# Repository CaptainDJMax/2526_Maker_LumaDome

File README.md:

# 2526_Maker_LumaDome

##  Présentation du projet
**LumaDome** est une lampe d'ambiance connectée et intelligente. L'objectif est d'allier esthétique et technique pour afficher des messages dynamiques. Conçue comme un objet design hybride, elle associe une base imprimée en 3D, un abat-jour textile structuré par découpe laser et l'électronique sur mesure et la gestion d'énergie.

Au-delà de l'esthétique, l'objectif est de créer une interface lumineuse capable de :
* Afficher des **notifications visuelles** (ex: simulateur d'aube au réveil).
* Diffuser des **messages personnalisés** envoyés en Bluetooth depuis un smartphone.
* Être totalement **nomade** grâce à une batterie intégrée.

## 🛠 Architecture Technique
Ce projet mobilise 4 axes principaux :
1.  **Mécanique :** Base cylindrique (Impression 3D) contenant l'électronique + Structure haute (Découpe Laser) supportant le textile.
2.  **Électronique :** PCB sur mesure avec microcontrôleur (type ESP32) pour la gestion LED et Bluetooth.
3.  **Énergie :** Système autonome sur batterie LiPo avec gestion de charge (BMS).
4.  **Habillage :** Travail du textile (Couture) pour la diffusion de la lumière.

##  Rétroplanning Prévisionnel 🔗[02_Gestion_Projet/RetroPlanning.md]

[Cliquez ici pour voir le rétroplanning complet et détaillé](./02_Gestion_Projet/RetroPlanning.md)

Ce planning s'aligne sur les séances de formation technique du semestre.

| Date | Phase | Objectifs spécifiques LumaDome |
| :--- | :--- | :--- |
| **19 Janv** | CAD (Conception) | Modélisation 3D de la base (support PCB) et esquisse de la structure laser. |
| **22 Janv** | 3D Print | Lancement de l'impression du prototype de la base. |
| **26 Janv** | Laser Cut | Découpe du squelette/cadre pour l'abat-jour. |
| **29 Janv** | PCB Design | Conception de la carte électronique (ESP32 + Driver LED). |
| **05 Fév** | Batterie (LiPo) | Dimensionnement de la batterie et intégration du BMS. |
| **09 Fév** | Couture | Patronage et assemblage du tissu sur la structure laser. |
| **Fév - Mars** |  Code & Finalisations| Développement du firmware (Bluetooth & Animations) + finalisation des choses pas terminer|
| **Avril** | Finalisation | Assemblage final, finitions et tournage vidéo. |

```mermaid
gantt
    title Rétro-Planning LumaDome (2026)
    dateFormat  YYYY-MM-DD
    axisFormat  %d/%m
    excludes    weekends

    section Phase 1 : Formation & Proto
    Git & Concept (Fait)       :done,    p1_git, 2026-01-15, 1d
    CAD Base 3D (En cours)     :active,  p1_cad, 2026-01-19, 3d
    3D Print (Lancement)       :         p1_3d,  2026-01-22, 1d
    Laser Cut (Structure)      :         p1_las, 2026-01-26, 3d
    PCB Design (KiCad)         :         p1_pcb, 2026-01-29, 4d
    Soudure & Routage          :         p1_sou, 2026-02-02, 3d
    Batterie LiPo & BMS        :         p1_bat, 2026-02-05, 4d
    Couture (Habillage)        :         p1_cou, 2026-02-09, 5d

    section Phase 2 : Dév. LumaDome
    Intégration Méca/Elec      :         p2_int, 2026-02-16, 3d
    Code (Hello World LED)     :         p2_dev1, 2026-02-19, 10d
    Code (Bluetooth BLE)       :         p2_dev2, 2026-03-09, 3d
    Debug & Tests Autonomie    :         p2_deb, 2026-03-12, 4d
    Finitions Tissu            :         p2_fin, 2026-03-16, 3d
    Code (Animations)          :         p2_dev3, 2026-03-19, 4d
    Assemblage Final           :         p2_ass, 2026-03-23, 3d
    Tournage Vidéo             :         p2_vid, 2026-03-26, 4d
    Derniers ajustements       :         p2_adj, 2026-03-30, 7d
    Prép. Soutenance           :         p2_sou, 2026-04-02, 7d
    
    section Jalons
    SOUTENANCE FINALE          :crit, milestone, 2026-04-13, 0d
```
---

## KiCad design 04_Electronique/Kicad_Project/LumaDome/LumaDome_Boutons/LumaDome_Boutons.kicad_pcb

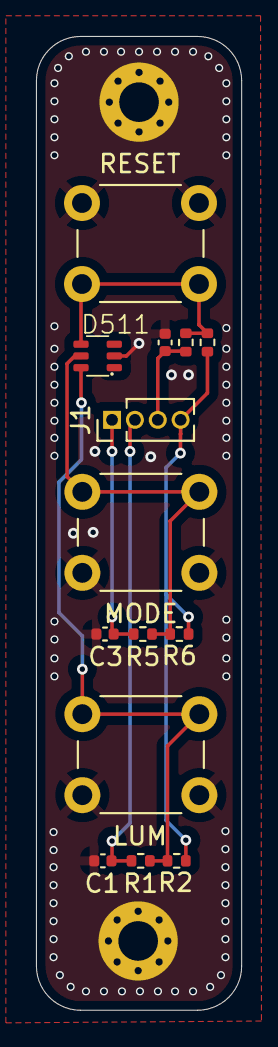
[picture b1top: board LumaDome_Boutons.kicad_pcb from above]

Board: 2 copper layers, 11.4 x 54.1 mm, 16 parts (0 on the bottom side), 8 nets.

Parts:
C1, C2, C3: 10n; C_0402_1005Metric
D511: WE 82402375; SC70-6L
H101, H102: MountingHole_Pad; MountingHole_2.2mm_M2_Pad_Via
J1: Conn_01x04; PinHeader_1x04_P1.27mm_Vertical
R1, R2, R3, R4, R5, R6: 10k; R_0402_1005Metric
SW1, SW2, SW3: SW_Push; SW_PUSH_6mm

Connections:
+3.3V: J1.4, R2.2, R4.2, R6.2
/Luminosity_b: D511.6 (I/O), R1.2, R2.1, SW3.1
/Luminosity_button: C1.1, J1.2, R1.1
/Mode_b: D511.5 (I/O), R5.2, R6.1, SW1.1
/Mode_button: C3.1, J1.1, R5.1
/Reset_b: D511.4 (I/O), R3.2, R4.1, SW2.1
/Reset_button: C2.1, J1.3, R3.1
GND: C1.2, C2.2, C3.2, D511.2 (GND), H101.1, H102.1, SW1.2, SW2.2, SW3.2

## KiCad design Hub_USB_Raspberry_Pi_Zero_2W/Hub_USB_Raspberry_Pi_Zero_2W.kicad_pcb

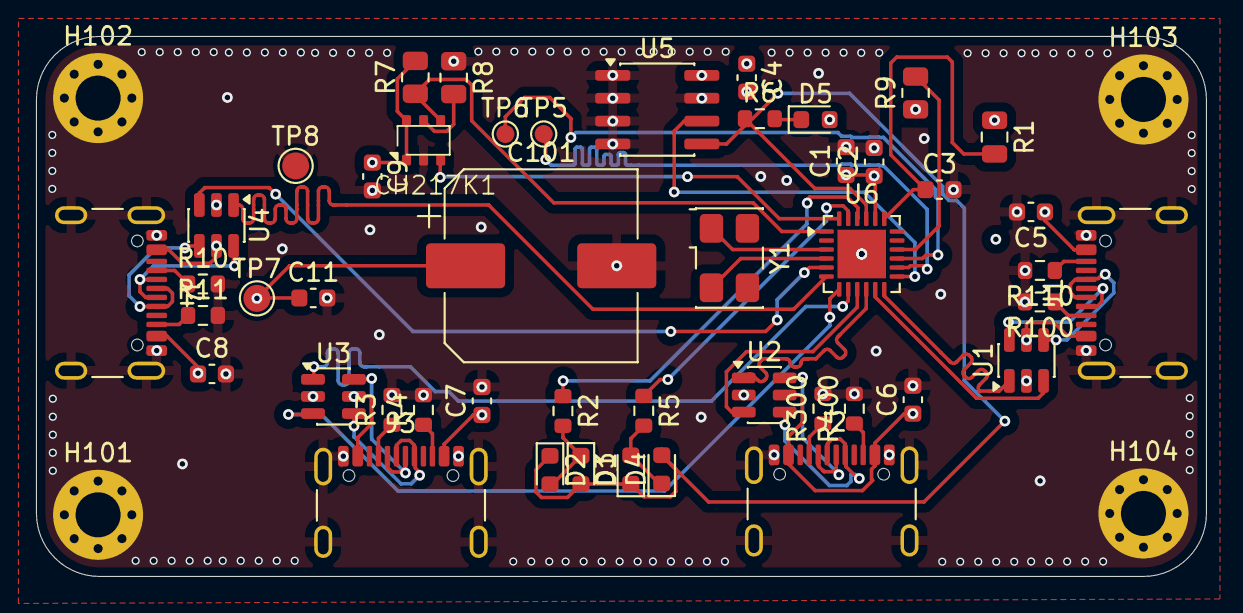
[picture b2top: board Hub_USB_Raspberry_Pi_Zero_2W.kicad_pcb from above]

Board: 4 copper layers, 65.0 x 30.0 mm, 51 parts (0 on the bottom side), 43 nets.

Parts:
C1, C3, C9: 10uF; C_0603_1608Metric
C2: 0.1uF; C_0603_1608Metric
C4: 100nF; C_0603_1608Metric
C5, C6, C7, C8: 100uF; C_0603_1608Metric
C11: 1uF; C_0603_1608Metric
C101: 470uF; CP_Elec_10x10.5
CH217K1: CH217K; CH217DS1
D1, D2, D3, D4: GREEN_LED; LED_0603_1608Metric
D5: RED_LED; LED_0603_1608Metric
H101, H102, H103, H104: MountingHole_Pad; MountingHole_2.5mm_Pad_Via
J1, J2, J3, J4: USB_C_Receptacle_USB2.0_16P; USB_C_Receptacle_GCT_USB4105-xx-A_16P_TopMnt_Horizontal
R1: 0; Fuse_0805_2012Metric
R2, R5: 220; R_0603_1608Metric
R3, R4, R10, R11, R100, R110, R300, R400: 5.1k; R_0603_1608Metric
R6: 10k; R_0603_1608Metric
R7: NC(56k); R_0805_2012Metric
R8: 56k; R_0805_2012Metric
R9: NC(4k7); R_0805_2012Metric
TP5: Data -; TestPoint_Pad_D1.0mm
TP6: Data +; TestPoint_Pad_D1.0mm
TP7: Alim; TestPoint_Pad_D1.5mm
TP8: Masse; TestPoint_Pad_D1.5mm
U1, U2, U3, U4: USBLC6-2SC6; SOT-23-6
U5: 24C02Cx-x-SN; SOIC-8_3.9x4.9mm_P1.27mm
U6: CH334F; QFN-24-1EP_4x4mm_P0.5mm_EP2.7x2.7mm
Y1: 12 MHZ; Crystal_SMD_5032-4Pin_5.0x3.2mm

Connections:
+3V3: C1.1, C2.1, C4.1, D5.2 (A), R9.1, U5.8 (VCC), U6.20 (VDD33_{LDO})
+5V: C5.1, C6.1, C7.1, C8.1, C9.1, C11.1, C101.1, CH217K1.1 (VIN), CH217K1.6 (VOUT), J1.A4 (VBUS), J1.A9 (VBUS), J1.B4 (VBUS), J1.B9 (VBUS), J2.A4 (VBUS), J2.A9 (VBUS), J2.B4 (VBUS), J2.B9 (VBUS), J3.A4 (VBUS), J3.A9 (VBUS), J3.B4 (VBUS), J3.B9 (VBUS), J4.A4 (VBUS), J4.A9 (VBUS), J4.B4 (VBUS), J4.B9 (VBUS), R1.1, R7.2, TP7.1, U1.5 (VBUS), U2.5 (VBUS), U3.5 (VBUS), U4.5 (VBUS)
/USB1/D+: J2.A6 (D+), J2.B6 (D+), U2.4 (I/O2)
/USB1/D-: J2.A7 (D-), J2.B7 (D-), U2.6 (I/O1)
/USB2/D+: J3.A6 (D+), J3.B6 (D+), U3.4 (I/O2)
/USB2/D-: J3.A7 (D-), J3.B7 (D-), U3.6 (I/O1)
/USB3/D+: J4.A6 (D+), J4.B6 (D+), U4.4 (I/O2)
/USB3/D-: J4.A7 (D-), J4.B7 (D-), U4.6 (I/O1)
/USB HUB controller/DM1-: U1.3 (I/O2), U6.11 (DM1-)
/USB HUB controller/DM2-: U2.3 (I/O2), U6.9 (DM2-)
/USB HUB controller/DM3-: U3.3 (I/O2), U6.7 (DM3-)
/USB HUB controller/DM4-: U4.3 (I/O2), U6.5 (DM4-)
/USB HUB controller/DP1+: U1.1 (I/O1), U6.12 (DP1+)
/USB HUB controller/DP2+: U2.1 (I/O1), U6.10 (DP2+)
/USB HUB controller/DP3+: U3.1 (I/O1), U6.8 (DP3+)
/USB HUB controller/DP4+: U4.1 (I/O1), U6.6 (DP4+)
/USB HUB controller/LED1: R2.1, U6.22 (LED1)
/USB HUB controller/LED2: R5.1, U6.23 (LED2)
/USB HUB controller/LED3/SCL: U5.6 (SCL), U6.13 (LED3/SCL)
/USB HUB controller/LED4/SDA: D1.2 (A), D2.1 (K), D3.1 (K), D4.2 (A), R6.1, U5.5 (SDA), U6.21 (LED4/SDA)
/USB HUB controller/OVCUR#: CH217K1.4 (FLAG#), R7.1, U6.1 (~OVCUR)
/USB HUB controller/~PWREN: CH217K1.3 (EN#), U6.24 (~PWREN)
/USB/D+: J1.A6 (D+), J1.B6 (D+), U1.4 (I/O2)
/USB/D-: J1.A7 (D-), J1.B7 (D-), U1.6 (I/O1)
GND: C1.2, C2.2, C3.2, C4.2, C5.2, C6.2, C7.2, C8.2, C9.2, C11.2, C101.2, CH217K1.2 (GND), H101.1, H102.1, H103.1, H104.1, J1.A1 (GND), J1.A12 (GND), J1.B1 (GND), J1.B12 (GND), J1.S1 (SHIELD), J2.A1 (GND), J2.A12 (GND), J2.B1 (GND), J2.B12 (GND), J2.S1 (SHIELD), J3.A1 (GND), J3.A12 (GND), J3.B1 (GND), J3.B12 (GND), J3.S1 (SHIELD), J4.A1 (GND), J4.A12 (GND), J4.B1 (GND), J4.B12 (GND), J4.S1 (SHIELD), R3.2, R4.2, R8.1, R10.2, R11.2, R100.2, R110.2, R300.2, R400.2, TP8.1, U1.2 (GND), U2.2 (GND), U3.2 (GND), U4.2 (GND), U5.1 (A0), U5.2 (A1), U5.3 (A2), U5.4 (GND), U5.7 (WP), U6.25 (GND)
unnamed: CH217K1.5 (ISET), R8.2
unnamed: D1.1 (K), D2.2 (A), R2.2
unnamed: D3.2 (A), D4.1 (K), R5.2
unnamed: D5.1 (K), R6.2
unnamed: J1.A5 (CC1), R100.1
unnamed: J1.B5 (CC2), R110.1
unnamed: J2.A5 (CC1), R300.1
unnamed: J2.B5 (CC2), R400.1
unnamed: J3.A5 (CC1), R3.1
unnamed: J3.B5 (CC2), R4.1
unnamed: J4.A5 (CC1), R10.1
unnamed: J4.B5 (CC2), R11.1
unnamed: TP5.1, U6.14 (DMU-)
unnamed: TP6.1, U6.15 (DPU+)
unnamed: C3.1, R1.2, U6.19 (V5)
unnamed: U6.4 (XI), Y1.2
unnamed: U6.3 (XO), Y1.1
unnamed: R9.2, U6.16 (~RESET/CDP)

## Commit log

2026-01-18 Initialisation structure LumaDome
2026-01-18 Ajout du retro planning et maj readme
2026-01-18 MAJ readme
2026-01-25 MAJ seance 3
2026-01-25 MAJ seance 3 + ajout photo
2026-01-28 Seance 04
2026-01-29 seance 5
2026-02-02 new pcb raspberry
2026-02-05 Update kicad HUB
2026-02-09 CB avançage
2026-02-09 Finalisation Routage PCB HUB
2026-02-16 seance 6et7 + finalisation Kicad
2026-03-09 Finalisation premier PCB
2026-05-05 Update and rename 05_Code to Lien_video_LumaDome
